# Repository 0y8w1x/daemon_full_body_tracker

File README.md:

# current version (tracker):

# current version (charger/updater):

# firmware
for understanding devicetree and bindings: https://github.com/lmapii/practical-zephyr/tree/main

# notes
to listen to UART: 
minicom -D /dev/ttyUSB0

update firmware over UART with: 
mcumgr-client -d /dev/ttyUSB0 -b 460800 upload build/zephyr/app_update.bin

list with:
mcumgr --conntype serial --connstring "/dev/ttyUSB0,baud=460800" image list

confirm with:
mcumgr --conntype serial --connstring "/dev/ttyUSB0,baud=460800" image confirm c14c40bec9b925ec950af9ccbd3282b68765baeb21c8a0d2d524de6d4da6c468

mcumgr-client -d /dev/ttyUSB0 -b 460800 reset

# NOTE: disabled error handling for "match transceive(&mut *port, &chunk)" in

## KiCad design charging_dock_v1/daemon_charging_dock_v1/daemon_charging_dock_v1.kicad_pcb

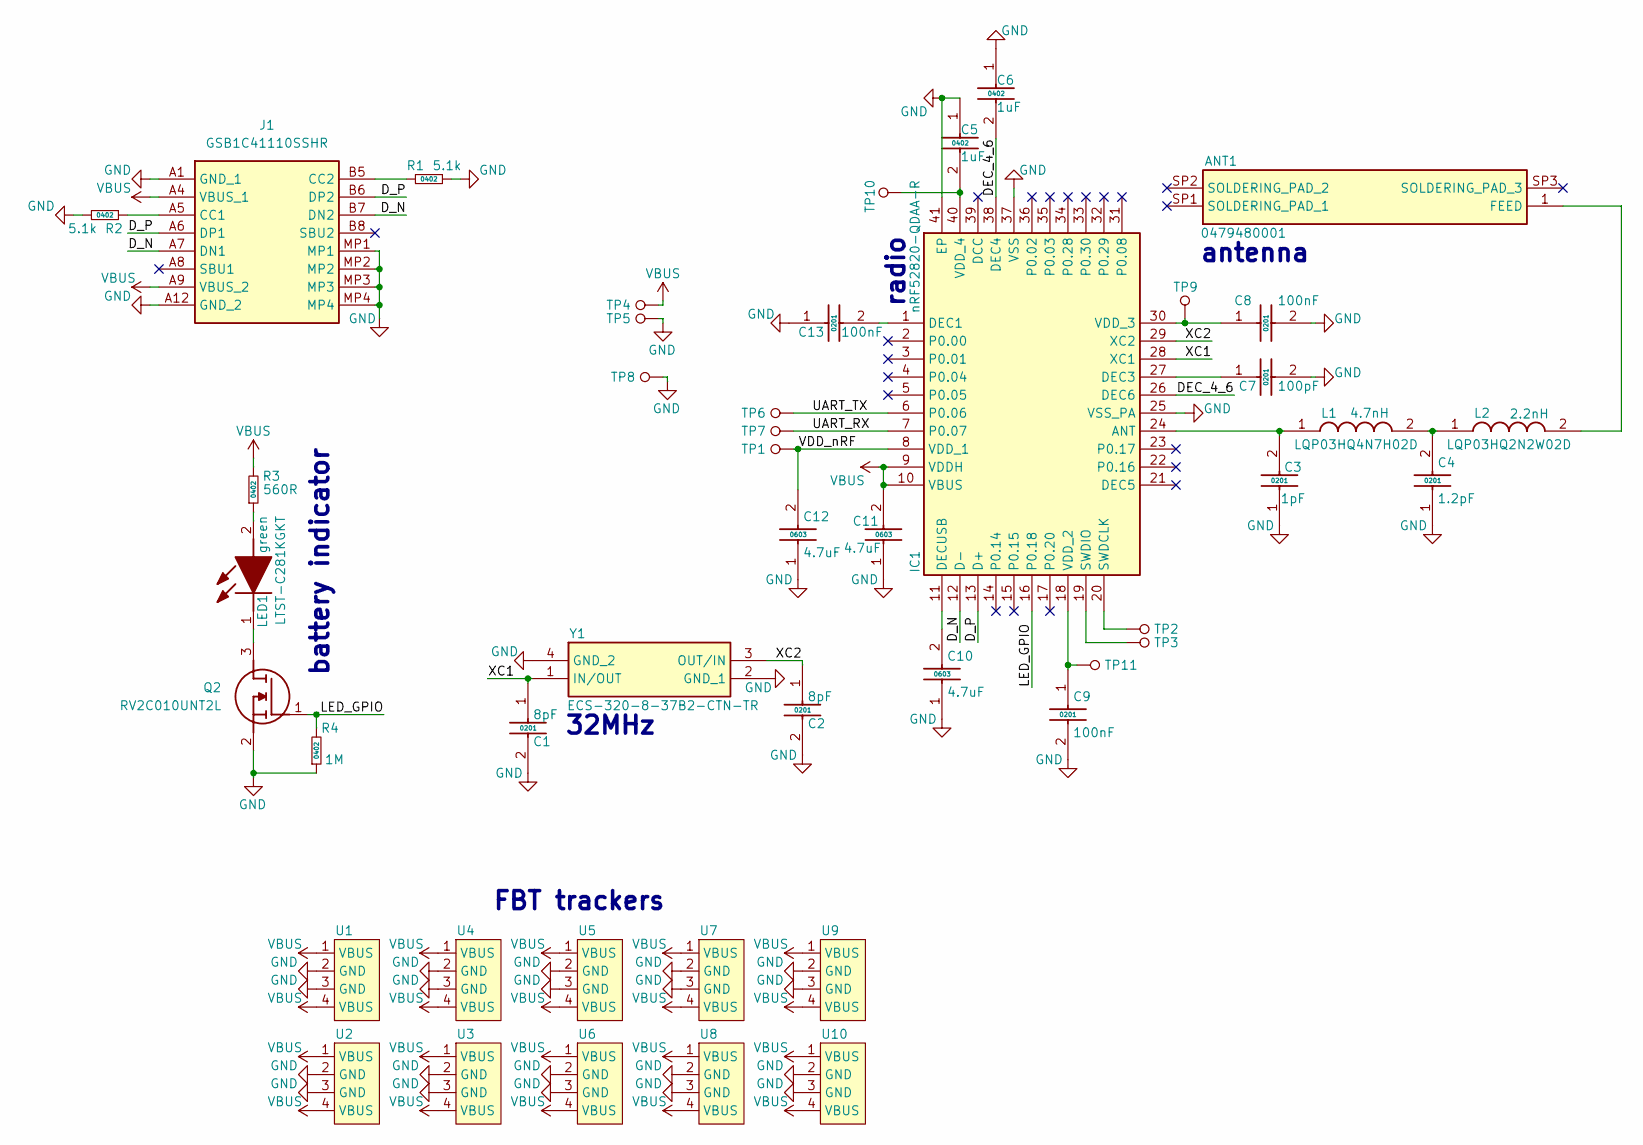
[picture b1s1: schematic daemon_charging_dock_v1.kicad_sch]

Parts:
ANT1: 0479480001; Manufacturer_Part_Number 0479480001; Mouser Part Number N/A
C1, C2: 8pF; CAPC0603X33N
C3: 1pF; CAPC0603X33N; Manufacturer_Part_Number GRM0335C1H1R0WA01D; Mouser Part Number 81-GRM0335C1H1R0WA1D
C4: 1.2pF; CAPC0603X33N; Manufacturer_Part_Number GRM0335C1H1R2WA01D; Mouser Part Number 81-GRM0335C1H1R2WA1D
C5, C6: 1uF; CAPC1005X55N; Manufacturer_Part_Number GRM155C71C105KE11J; Mouser Part Number 81-GRM155C71C105KE11
C7: 100pF; CAPC0603X33N; Manufacturer_Part_Number GRM0335C1E101FA01J; Mouser Part Number 81-GRM0335C1E101FA1J
C8, C9, C13: 100nF; CAPC0603X33N; Manufacturer_Part_Number GRM033R61E104KE14J; Mouser Part Number 81-GRM033R61E104KE4J
C10, C11, C12: 4.7uF; CAPC1608X90N; Manufacturer_Part_Number GRM188Z71C475KE21D; Mouser Part Number 81-GRM188Z71C475KE1D
IC1: nRF52820-QDAA-R; QFN40P500X500X90-41N-D; Manufacturer_Part_Number nRF52820-QDAA-R; Mouser Part Number 949-NRF52820-QDAA-R
J1: GSB1C41110SSHR; Manufacturer_Part_Number GSB1C41110SSHR
L1: 4.7nH; LQP03HQ0N5B02D; Manufacturer_Part_Number LQP03HQ4N7H02D; Mouser Part Number 81-LQP03HQ4N7H02D
L2: 2.2nH; LQP03HQ0N5B02D; Manufacturer_Part_Number LQP03HQ2N2W02D; Mouser Part Number 81-LQP03HQ2N2W02D
LED1: green; LEDC1005X35N; Manufacturer_Part_Number LTST-C281KGKT; Mouser Part Number 859-LTST-C281KGKT
Q2: RV2C010UNT2L; Manufacturer_Part_Number RV2C010UNT2L; Mouser Part Number 755-RV2C010UNT2L
R1, R2: 5.1k; 0402_res
R3: 560R; 0402_res
R4: 1M; 0402_res
TP1, TP2, TP3, TP4, TP5, TP6, TP7, TP8, TP9, TP10, TP11: tp_1mm
U1, U2, U3, U4, U5, U6, U7, U8, U9, U10: fbt_tracker
Y1: ECS-320-8-37B2-CTN-TR; ECS320837B2CTNTR; Manufacturer_Part_Number ECS-320-8-37B2-CTN-TR; Mouser Part Number 520-320-8-37B2-CTNTR

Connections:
/DEC_4_6: C6.2, IC1.26 (DEC6), IC1.38 (DEC4)
/D_N: IC1.12 (D-), J1.A7 (DN1), J1.B7 (DN2)
/D_P: IC1.13 (D+), J1.A6 (DP1), J1.B6 (DP2)
/LED_GPIO: IC1.16 (P0.18), Q2.1 (G), R4.2
/UART_RX: IC1.7 (P0.07), TP7.1
/UART_TX: IC1.6 (P0.06), TP6.1
/VDD_nRF: C12.2, IC1.8 (VDD_1), TP1.1
/XC1: C1.1, IC1.28 (XC1), Y1.1 (IN/OUT)
/XC2: C2.1, IC1.29 (XC2), Y1.3 (OUT/IN)
GND: C1.2, C2.2, C3.1, C4.1, C5.1, C6.1, C7.2, C8.2, C9.2, C10.1, C11.1, C12.1, C13.1, IC1.25 (VSS_PA), IC1.37 (VSS), IC1.41 (EP), J1.A1 (GND_1), J1.A12 (GND_2), J1.MP1, J1.MP2, J1.MP3, J1.MP4, Q2.2 (S), R1.2, R2.2, R4.1, TP5.1, TP8.1, U1.2 (GND), U1.3 (GND), U2.2 (GND), U2.3 (GND), U3.2 (GND), U3.3 (GND), U4.2 (GND), U4.3 (GND), U5.2 (GND), U5.3 (GND), U6.2 (GND), U6.3 (GND), U7.2 (GND), U7.3 (GND), U8.2 (GND), U8.3 (GND), U9.2 (GND), U9.3 (GND), U10.2 (GND), U10.3 (GND), Y1.2 (GND_1), Y1.4 (GND_2)
unnamed: ANT1.1 (FEED), L2.2
unnamed: C4.2, L1.2, L2.1
unnamed: C3.2, IC1.24 (ANT), L1.1
unnamed: C13.2, IC1.1 (DEC1)
unnamed: C7.1, IC1.27 (DEC3)
unnamed: C10.2, IC1.11 (DECUSB)
unnamed: IC1.20 (SWDCLK), TP2.1
unnamed: IC1.19 (SWDIO), TP3.1
unnamed: C9.1, IC1.18 (VDD_2), TP11.1
unnamed: C8.1, IC1.30 (VDD_3), TP9.1
unnamed: C5.2, IC1.40 (VDD_4), TP10.1
unnamed: J1.A5 (CC1), R2.1
unnamed: J1.B5 (CC2), R1.1
unnamed: LED1.2 (A), R3.1
unnamed: LED1.1 (K), Q2.3 (D)
VBUS: C11.2, IC1.9 (VDDH), IC1.10 (VBUS), J1.A4 (VBUS_1), J1.A9 (VBUS_2), R3.2, TP4.1, U1.1 (VBUS), U1.4 (VBUS), U2.1 (VBUS), U2.4 (VBUS), U3.1 (VBUS), U3.4 (VBUS), U4.1 (VBUS), U4.4 (VBUS), U5.1 (VBUS), U5.4 (VBUS), U6.1 (VBUS), U6.4 (VBUS), U7.1 (VBUS), U7.4 (VBUS), U8.1 (VBUS), U8.4 (VBUS), U9.1 (VBUS), U9.4 (VBUS), U10.1 (VBUS), U10.4 (VBUS)

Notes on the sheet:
32MHz
battery indicator
radio
antenna
FBT trackers

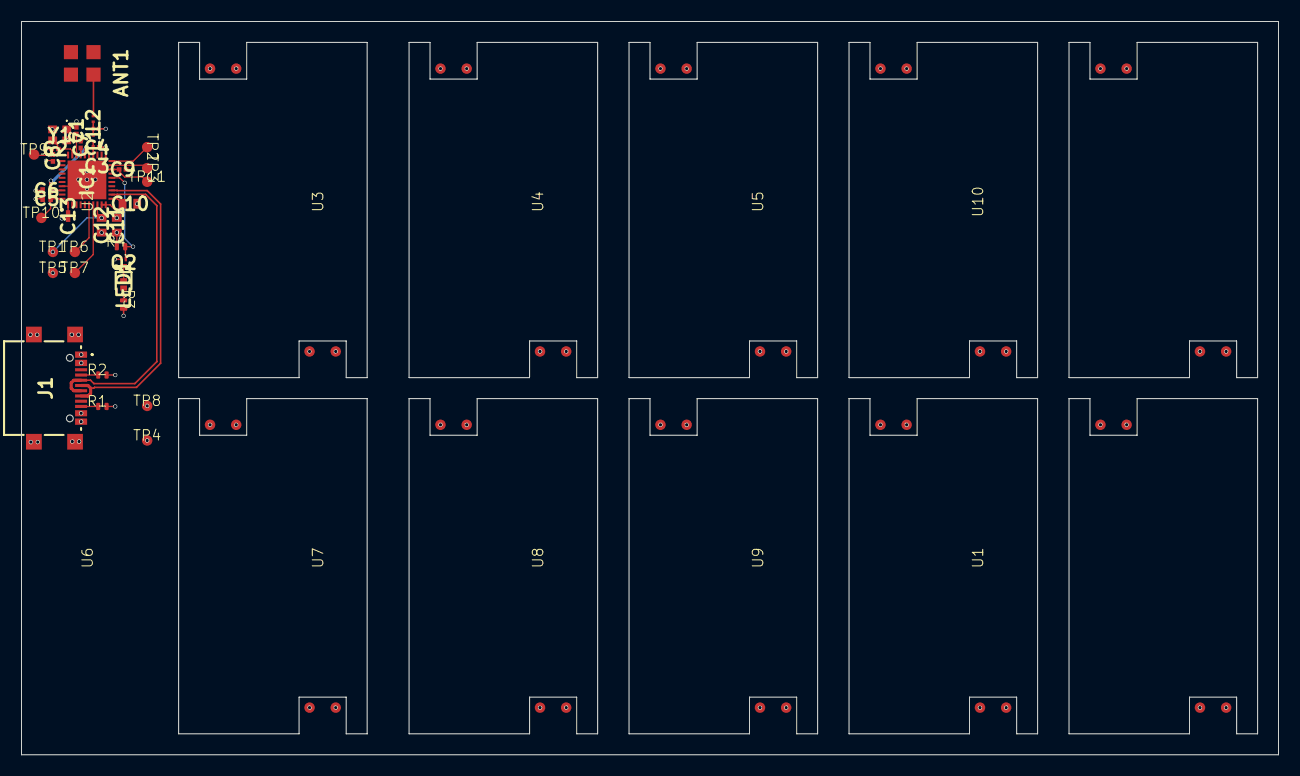
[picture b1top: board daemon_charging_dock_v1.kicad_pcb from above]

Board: 4 copper layers, 120.0 x 70.0 mm, 46 parts (0 on the bottom side), 26 nets.

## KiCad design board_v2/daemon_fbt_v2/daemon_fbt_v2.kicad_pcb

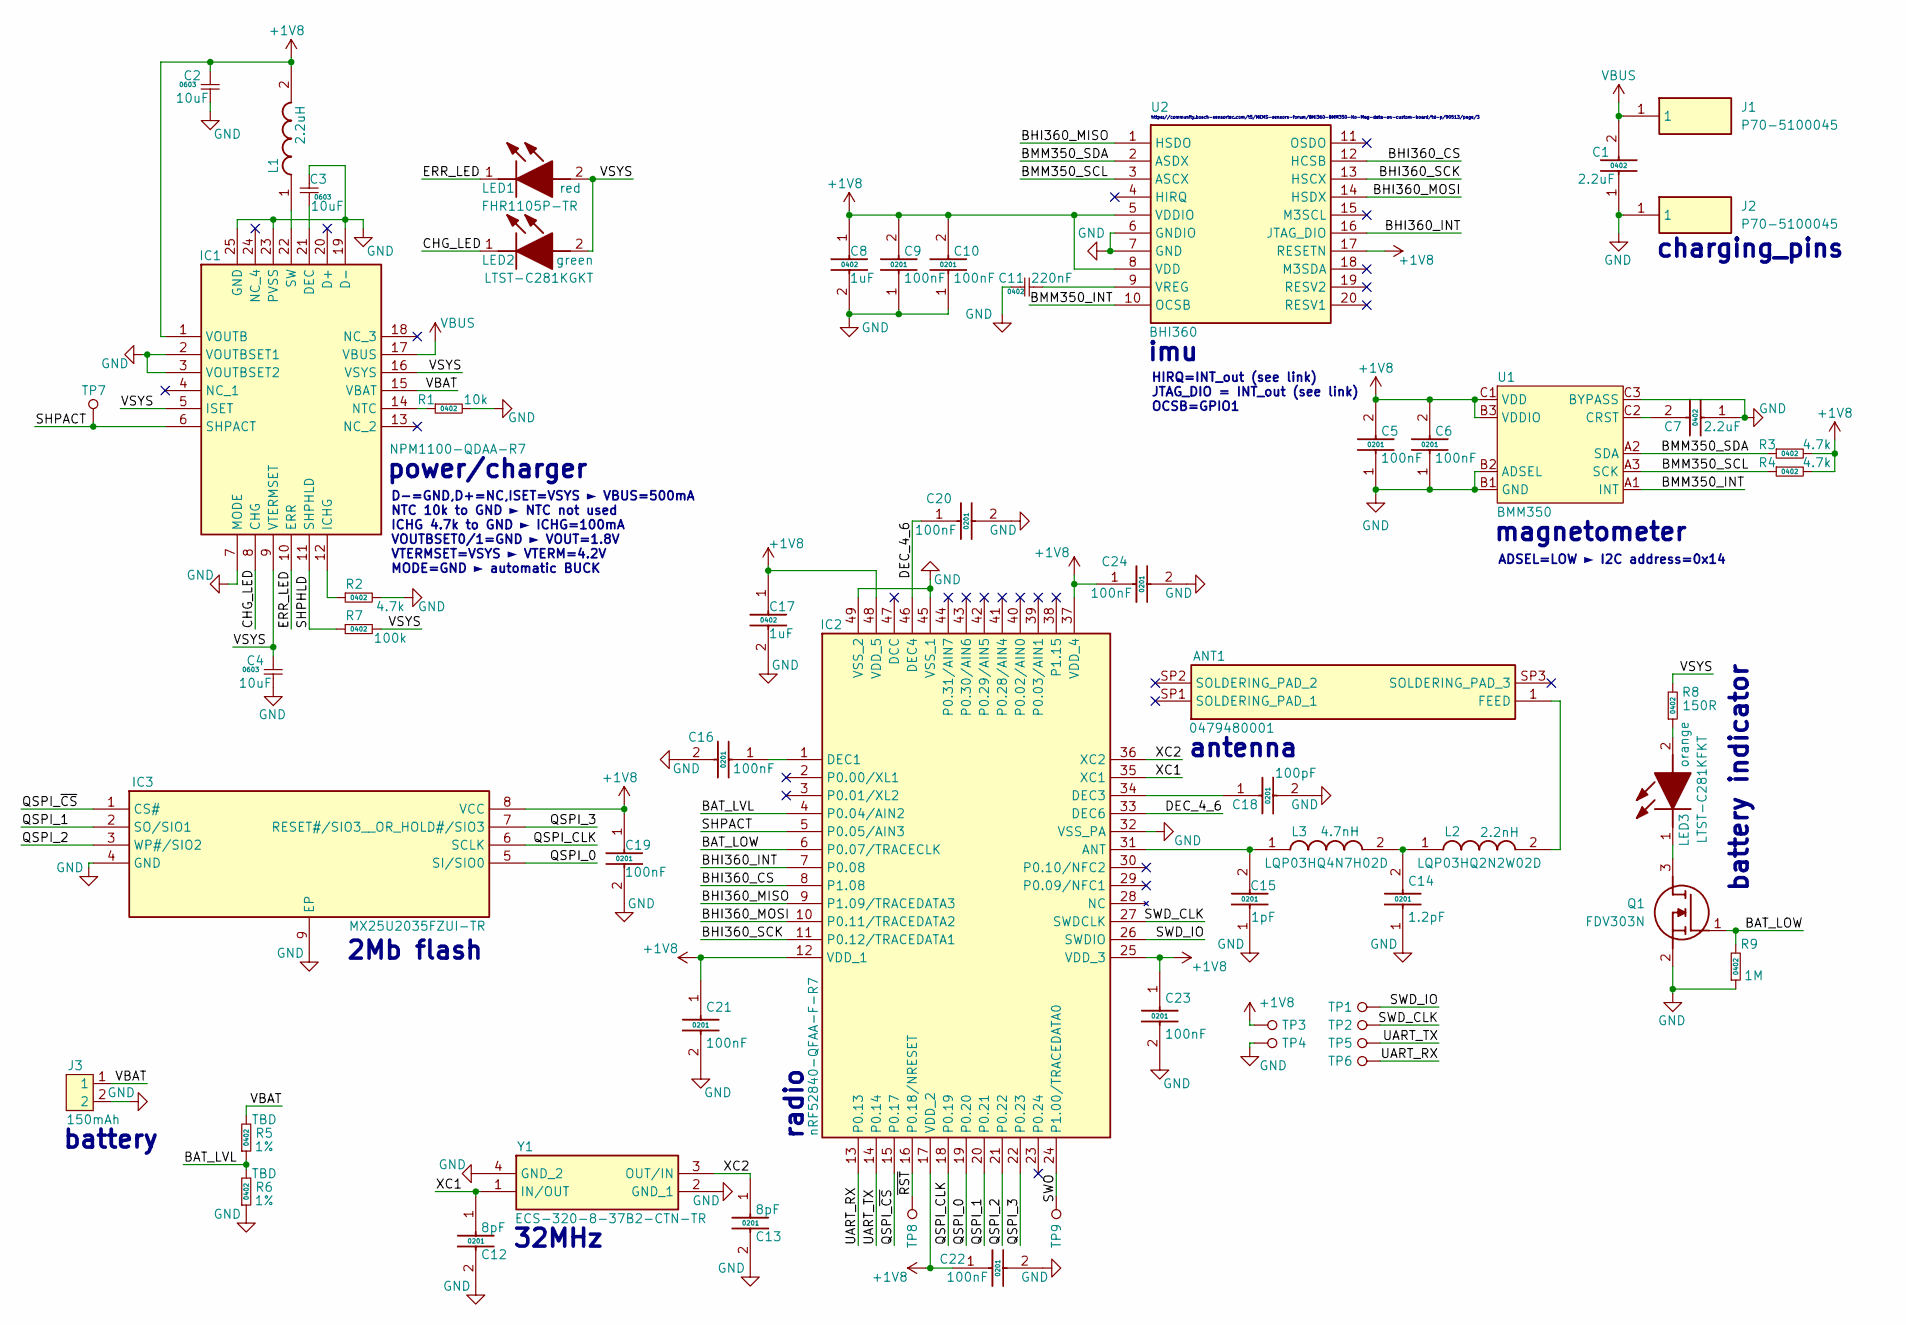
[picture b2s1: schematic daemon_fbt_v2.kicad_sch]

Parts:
ANT1: 0479480001; Manufacturer_Part_Number 0479480001; Mouser Part Number N/A
C1, C7: 2.2uF; CAPC1005X55N; Manufacturer_Part_Number GRM155R61A225KE01J; Mouser Part Number 81-GRM155R61A225K01J
C2, C3, C4: 10uF; 0603_cap
C5, C6, C9, C10, C16, C19, C20, C21, C22, C23, C24: 100nF; CAPC0603X33N; Manufacturer_Part_Number GRM033R61E104KE14J; Mouser Part Number 81-GRM033R61E104KE4J
C8, C17: 1uF; CAPC1005X55N; Manufacturer_Part_Number GRM155C71C105KE11J; Mouser Part Number 81-GRM155C71C105KE11
C11: 220nF; 0402_cap
C12, C13: 8pF; CAPC0603X33N
C14: 1.2pF; CAPC0603X33N; Manufacturer_Part_Number GRM0335C1H1R2WA01D; Mouser Part Number 81-GRM0335C1H1R2WA1D
C15: 1pF; CAPC0603X33N; Manufacturer_Part_Number GRM0335C1H1R0WA01D; Mouser Part Number 81-GRM0335C1H1R0WA1D
C18: 100pF; CAPC0603X33N; Manufacturer_Part_Number GRM0335C1E101FA01J; Mouser Part Number 81-GRM0335C1E101FA1J
IC1: NPM1100-QDAA-R7; QFN50P400X400X90-25N-D; Manufacturer_Part_Number NPM1100-QDAA-R7; Mouser Part Number 949-NPM1100-QDAA-R7
IC2: nRF52840-QFAA-F-R7; QFN40P600X600X95-49N-D; Manufacturer_Part_Number nRF52840-QFAA-F-R7; Mouser Part Number 949-NRF52840QFAAF-R7
IC3: MX25U2035FZUI-TR; SON50P200X300X60-9N; Manufacturer_Part_Number MX25U2035FZUI-TR; Mouser Part Number MX25U2035FZUI-TR
J1, J2: P70-5100045; P705100045; Manufacturer_Part_Number P70-5100045; Mouser Part Number 855-P70-5100045
J3: 150mAh; battery_150mAh
L1: 2.2uH; INDC2012X105N; Manufacturer_Part_Number MLZ2012N2R2LT000; Mouser Part Number 810-MLZ2012N2R2LT000
L2: 2.2nH; LQP03HQ0N5B02D; Manufacturer_Part_Number LQP03HQ2N2W02D; Mouser Part Number 81-LQP03HQ2N2W02D
L3: 4.7nH; LQP03HQ0N5B02D; Manufacturer_Part_Number LQP03HQ4N7H02D; Mouser Part Number 81-LQP03HQ4N7H02D
LED1: red; FHR1105PTR; Manufacturer_Part_Number FHR1105P-TR; Mouser Part Number 327-FHR1105PTR
LED2: green; LEDC1005X35N; Manufacturer_Part_Number LTST-C281KGKT; Mouser Part Number 859-LTST-C281KGKT
LED3: orange; LEDC1005X35N
Q1: FDV303N; SOT96P237X111-3N; Manufacturer_Part_Number FDV303N; Mouser Part Number 512-FDV303N
R1: 10k; 0402_res
R2, R3, R4: 4.7k; 0402_res
R5, R6: TBD; 0402_res; Tolerance 1%
R7: 100k; 0402_res
R8: 150R; 0402_res
R9: 1M; 0402_res
TP1, TP2, TP3, TP4, TP5, TP6, TP7, TP8, TP9: tp_1mm
U1: BMM350
U2: BHI360; Manufacturer_Part_Number BHI360; Mouser Part Number 262-BHI360
Y1: ECS-320-8-37B2-CTN-TR; ECS320837B2CTNTR; Manufacturer_Part_Number ECS-320-8-37B2-CTN-TR; Mouser Part Number 520-320-8-37B2-CTNTR

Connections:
+1V8: C2.2, C5.2, C6.2, C8.1, C9.2, C10.2, C17.1, C19.1, C21.1, C22.1, C23.1, C24.1, IC1.1 (VOUTB), IC2.12 (VDD_1), IC2.17 (VDD_2), IC2.25 (VDD_3), IC2.37 (VDD_4), IC2.48 (VDD_5), IC3.8 (VCC), L1.2, R3.2, R4.2, TP3.1, U1.B3 (VDDIO), U1.C1 (VDD), U2.5 (VDDIO), U2.8 (VDD), U2.17 (RESETN)
/BAT_LOW: IC2.6 (P0.07/TRACECLK), Q1.1 (G), R9.2
/BAT_LVL: IC2.4 (P0.04/AIN2), R5.1, R6.2
/BHI360_CS: IC2.8 (P1.08), U2.12 (HCSB)
/BHI360_INT: IC2.7 (P0.08), U2.16 (JTAG_DIO)
/BHI360_MISO: IC2.9 (P1.09/TRACEDATA3), U2.1 (HSDO)
/BHI360_MOSI: IC2.10 (P0.11/TRACEDATA2), U2.14 (HSDX)
/BHI360_SCK: IC2.11 (P0.12/TRACEDATA1), U2.13 (HSCX)
/BMM350_INT: U1.A1 (INT), U2.10 (OCSB)
/BMM350_SCL: R4.1, U1.A3 (SCK), U2.3 (ASCX)
/BMM350_SDA: R3.1, U1.A2 (SDA), U2.2 (ASDX)
/CHG_LED: IC1.8 (CHG), LED2.1 (K)
/DEC_4_6: C20.1, IC2.33 (DEC6), IC2.46 (DEC4)
/ERR_LED: IC1.10 (ERR), LED1.1 (K)
/QSPI_0: IC2.19 (P0.20), IC3.5 (SI/SIO0)
/QSPI_1: IC2.20 (P0.21), IC3.2 (SO/SIO1)
/QSPI_2: IC2.21 (P0.22), IC3.3 (WP#/SIO2)
/QSPI_3: IC2.22 (P0.23), IC3.7 (RESET#/SIO3__OR_HOLD#/SIO3)
/QSPI_CLK: IC2.18 (P0.19), IC3.6 (SCLK)
/QSPI_~CS: IC2.15 (P0.17), IC3.1 (CS#)
/SHPACT: IC1.6 (SHPACT), IC2.5 (P0.05/AIN3), TP7.1
/SHPHLD: IC1.11 (SHPHLD), R7.1
/SWD_CLK: IC2.27 (SWDCLK), TP2.1
/SWD_IO: IC2.26 (SWDIO), TP1.1
/SWO: IC2.24 (P1.00/TRACEDATA0), TP9.1
/UART_RX: IC2.13 (P0.13), TP6.1
/UART_TX: IC2.14 (P0.14), TP5.1
/VBAT: IC1.15 (VBAT), J3.1, R5.2
/VSYS: C4.2, IC1.5 (ISET), IC1.9 (VTERMSET), IC1.16 (VSYS), LED1.2 (A), LED2.2 (A), R7.2, R8.2
/XC1: C12.1, IC2.35 (XC1), Y1.1 (IN/OUT)
/XC2: C13.1, IC2.36 (XC2), Y1.3 (OUT/IN)
/~RST: IC2.16 (P0.18/NRESET), TP8.1
GND: C1.1, C2.1, C3.2, C4.1, C5.1, C6.1, C7.1, C8.2, C9.1, C10.1, C11.2, C12.2, C13.2, C14.1, C15.1, C16.2, C17.2, C18.2, C19.2, C20.2, C21.2, C22.2, C23.2, C24.2, IC1.2 (VOUTBSET1), IC1.3 (VOUTBSET2), IC1.7 (MODE), IC1.19 (D-), IC1.23 (PVSS), IC1.25 (GND), IC2.32 (VSS_PA), IC2.45 (VSS_1), IC2.49 (VSS_2), IC3.4 (GND), IC3.9 (EP), J2.1, J3.2, Q1.2 (S), R1.2, R2.2, R6.1, R9.1, TP4.1, U1.B1 (GND), U1.B2 (ADSEL), U1.C3 (BYPASS), U2.6 (GNDIO), U2.7 (GND), Y1.2 (GND_1), Y1.4 (GND_2)
unnamed: ANT1.1 (FEED), L2.2
unnamed: C14.2, L2.1, L3.2
unnamed: C3.1, IC1.21 (DEC)
unnamed: IC1.12 (ICHG), R2.1
unnamed: IC1.14 (NTC), R1.1
unnamed: IC1.22 (SW), L1.1
unnamed: C15.2, IC2.31 (ANT), L3.1
unnamed: C16.1, IC2.1 (DEC1)
unnamed: C18.1, IC2.34 (DEC3)
unnamed: LED3.2 (A), R8.1
unnamed: LED3.1 (K), Q1.3 (D)
unnamed: C7.2, U1.C2 (CRST)
unnamed: C11.1, U2.9 (VREG)
VBUS: C1.2, IC1.17 (VBUS), J1.1

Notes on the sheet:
battery
D-=GND,D+=NC,ISET=VSYS ► VBUS=500mA NTC 10k to GND ► NTC not used ICHG 4.7k to GND ► ICHG=100mA VOUTBSET0/1=GND ► VOUT=1.8V VTERMSET=VSYS ► VTERM=4.2V MODE=GND ► automatic BUCK
ADSEL=LOW ► I2C address=0x14
https://community.bosch-sensortec.com/t5/MEMS-sensors-forum/BHI360-BMM350-No-Mag-data-on-custom-board/td-p/90513/page/3
battery indicator
32MHz
antenna
HIRQ=INT_out (see link) JTAG_DIO = INT_out (see link) OCSB=GPIO1
magnetometer
radio
2Mb flash
charging_pins
imu
power/charger

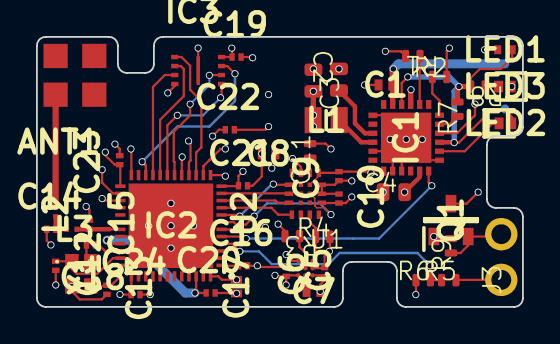
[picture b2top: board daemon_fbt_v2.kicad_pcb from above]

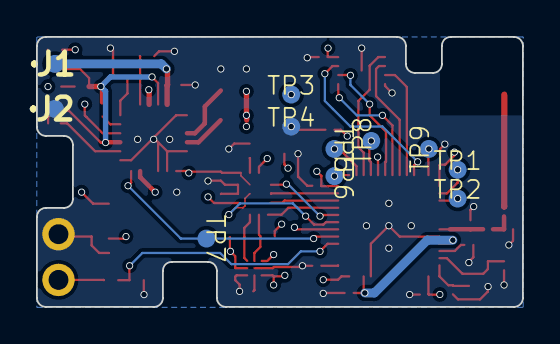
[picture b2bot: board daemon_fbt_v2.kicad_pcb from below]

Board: 4 copper layers, 27.0 x 15.0 mm, 59 parts (11 on the bottom side), 47 nets.

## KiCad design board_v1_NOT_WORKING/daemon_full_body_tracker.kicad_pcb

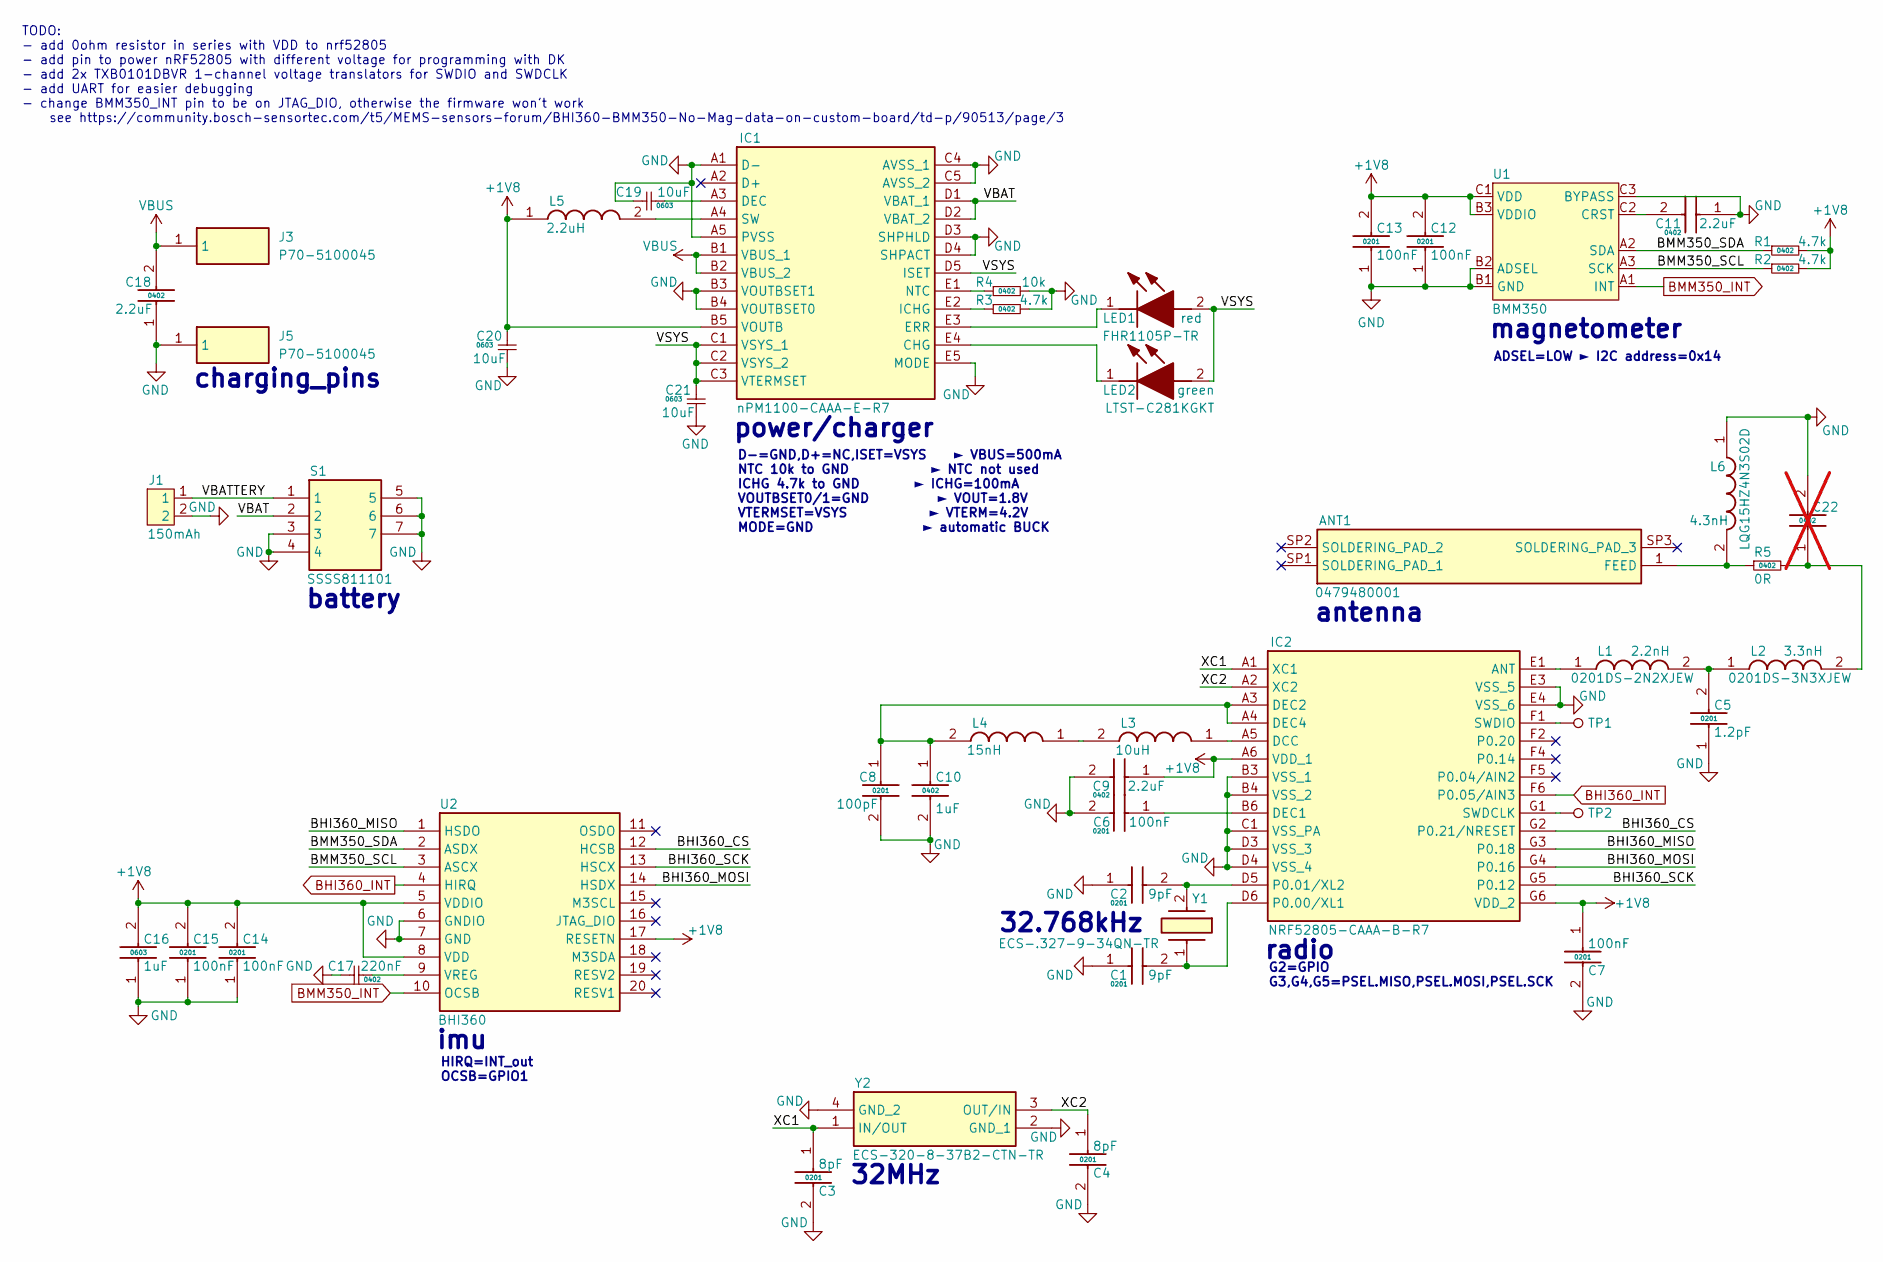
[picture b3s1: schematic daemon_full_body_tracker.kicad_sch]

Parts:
ANT1: 0479480001; Manufacturer_Part_Number 0479480001; Mouser Part Number N/A
C1, C2: 9pF; CAPC0603X33N
C3, C4: 8pF; CAPC0603X33N
C5: 1.2pF; CAPC0603X33N; Manufacturer_Part_Number GRM0335C1E1R2BA01D; Mouser Part Number 81-GRM0335C1E1R2BA1D
C6, C7, C12, C13, C14, C15: 100nF; CAPC0603X33N; Manufacturer_Part_Number GRM033R61E104KE14J; Mouser Part Number 81-GRM033R61E104KE4J
C8: 100pF; CAPC0603X33N; Manufacturer_Part_Number GRM0335C1E101FA01J; Mouser Part Number 81-GRM0335C1E101FA1J
C9, C11, C18: 2.2uF; CAPC1005X55N; Manufacturer_Part_Number GRM155R61E225KE11D; Mouser Part Number 81-GRM155R61E225KE1D
C10: 1uF; CAPC1005X55N; Manufacturer_Part_Number GRM155C71C105KE11J; Mouser Part Number 81-GRM155C71C105KE11
C16: 1uF; CAPC1608X90N; Manufacturer_Part_Number 0603ZD105JAT2A; Mouser Part Number 581-0603ZD105JAT2A
C17: 220nF; 0402_cap
C19, C20, C21: 10uF; 0603_cap
C22: CAPC1005X55N; Manufacturer_Part_Number GRM155C71C105KE11J; Mouser Part Number 81-GRM155C71C105KE11; not fitted
IC1: nPM1100-CAAA-E-R7; BGA25C40P5X5_208X208X52; Manufacturer_Part_Number nPM1100-CAAA-E-R7; Mouser Part Number 949-NPM1100-CAAA-R7
IC2: NRF52805-CAAA-B-R7; NRF52805CAAAR7
J1: 150mAh; battery_150mAh
J3, J5: P70-5100045; P705100045; Manufacturer_Part_Number P70-5100045; Mouser Part Number 855-P70-5100045
L1: 2.2nH; INDC0605X45N; Manufacturer_Part_Number 0201DS-2N2XJEW; Mouser Part Number 994-0201DS-2N2XJEW
L2: 3.3nH; INDC0605X45N; Manufacturer_Part_Number 0201DS-3N3XJEW; Mouser Part Number 994-0201DS-3N3XJEW
L3: 10uH; INDM2520X190N; Manufacturer_Part_Number NLV25T-100J-EF; Mouser Part Number 810-NLV25T-100J-EF
L4: 15nH; LQW15CNR20J00B; Manufacturer_Part_Number LQW15AN15NH00D; Mouser Part Number 81-LQW15AN15NH00D
L5: 2.2uH; INDC2012X105N; Manufacturer_Part_Number MLZ2012N2R2LT000; Mouser Part Number 810-MLZ2012N2R2LT000
L6: 4.3nH; LQG15WH0N7B02D; Manufacturer_Part_Number LQG15HZ4N3S02D
LED1: red; FHR1105PTR; Manufacturer_Part_Number FHR1105P-TR; Mouser Part Number 327-FHR1105PTR
LED2: green; LEDC1005X35N; Manufacturer_Part_Number LTST-C281KGKT; Mouser Part Number 859-LTST-C281KGKT
R1, R2, R3: 4.7k; 0402_res
R4: 10k; 0402_res
R5: 0R; 0402_res
S1: SSSS811101; Manufacturer_Part_Number SSSS811101; Mouser Part Number 688-SSSS811101
TP1, TP2: tp_1mm
U1: BMM350
U2: BHI360; Manufacturer_Part_Number BHI360; Mouser Part Number 262-BHI360
Y1: ECS-.327-9-34QN-TR; ECS327934QNTR; Manufacturer_Part_Number ECS-.327-9-34QN-TR; Mouser Part Number 520-.327-9-34QNT
Y2: ECS-320-8-37B2-CTN-TR; ECS320837B2CTNTR; Manufacturer_Part_Number ECS-320-8-37B2-CTN-TR; Mouser Part Number 520-320-8-37B2-CTNTR

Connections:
+1V8: C7.1, C9.1, C12.2, C13.2, C14.2, C15.2, C16.2, C20.2, IC1.B5 (VOUTB), IC2.A6 (VDD_1), IC2.G6 (VDD_2), L5.1, R1.2, R2.2, U1.B3 (VDDIO), U1.C1 (VDD), U2.5 (VDDIO), U2.8 (VDD), U2.17 (RESETN)
/BHI360_CS: IC2.G2 (P0.21/NRESET), U2.12 (HCSB)
/BHI360_MISO: IC2.G3 (P0.18), U2.1 (HSDO)
/BHI360_MOSI: IC2.G4 (P0.16), U2.14 (HSDX)
/BHI360_SCK: IC2.G5 (P0.12), U2.13 (HSCX)
/BMM350_SCL: R2.1, U1.A3 (SCK), U2.3 (ASCX)
/BMM350_SDA: R1.1, U1.A2 (SDA), U2.2 (ASDX)
/VBAT: IC1.D1 (VBAT_1), IC1.D2 (VBAT_2), S1.2
/VBATTERY: J1.1, S1.1
/VSYS: C21.2, IC1.C1 (VSYS_1), IC1.C2 (VSYS_2), IC1.C3 (VTERMSET), IC1.D5 (ISET), LED1.2 (A), LED2.2 (A)
/XC1: C3.1, IC2.A1 (XC1), Y2.1 (IN/OUT)
/XC2: C4.1, IC2.A2 (XC2), Y2.3 (OUT/IN)
BHI360_INT: IC2.F6 (P0.05/AIN3), U2.4 (HIRQ)
BMM350_INT: U1.A1 (INT), U2.10 (OCSB)
GND: C1.1, C2.1, C3.2, C4.2, C5.1, C6.2, C7.2, C8.2, C9.2, C10.2, C11.1, C12.1, C13.1, C14.1, C15.1, C16.1, C17.2, C18.1, C19.1, C20.1, C21.1, C22.2, IC1.A1 (D-), IC1.A5 (PVSS), IC1.B3 (VOUTBSET1), IC1.B4 (VOUTBSET0), IC1.C4 (AVSS_1), IC1.C5 (AVSS_2), IC1.D3 (SHPHLD), IC1.D4 (SHPACT), IC1.E5 (MODE), IC2.B3 (VSS_1), IC2.B4 (VSS_2), IC2.C1 (VSS_PA), IC2.D3 (VSS_3), IC2.D4 (VSS_4), IC2.E3 (VSS_5), IC2.E4 (VSS_6), J1.2, J5.1, L6.1, R3.2, R4.2, S1.3, S1.4, S1.5, S1.6, S1.7, U1.B1 (GND), U1.B2 (ADSEL), U1.C3 (BYPASS), U2.6 (GNDIO), U2.7 (GND), Y2.2 (GND_1), Y2.4 (GND_2)
unnamed: ANT1.1 (FEED), L6.2, R5.1
unnamed: C5.2, L1.2, L2.1
unnamed: C22.1, L2.2, R5.2
unnamed: IC1.E4 (CHG), LED2.1 (K)
unnamed: C19.2, IC1.A3 (DEC)
unnamed: IC1.E3 (ERR), LED1.1 (K)
unnamed: IC1.E2 (ICHG), R3.1
unnamed: IC1.E1 (NTC), R4.1
unnamed: IC1.A4 (SW), L5.2
unnamed: IC2.E1 (ANT), L1.1
unnamed: IC2.A5 (DCC), L3.1
unnamed: C6.1, IC2.B6 (DEC1)
unnamed: C8.1, C10.1, IC2.A3 (DEC2), IC2.A4 (DEC4), L4.2
unnamed: C1.2, IC2.D6 (P0.00/XL1), Y1.1 (OUT/IN)
unnamed: C2.2, IC2.D5 (P0.01/XL2), Y1.2 (OUT/IN)
unnamed: IC2.G1 (SWDCLK), TP2.1
unnamed: IC2.F1 (SWDIO), TP1.1
unnamed: L3.2, L4.1
unnamed: C11.2, U1.C2 (CRST)
unnamed: C17.1, U2.9 (VREG)
VBUS: C18.2, IC1.B1 (VBUS_1), IC1.B2 (VBUS_2), J3.1

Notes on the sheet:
D-=GND,D+=NC,ISET=VSYS ► VBUS=500mA NTC 10k to GND ► NTC not used ICHG 4.7k to GND ► ICHG=100mA VOUTBSET0/1=GND ► VOUT=1.8V VTERMSET=VSYS ► VTERM=4.2V MODE=GND ► automatic BUCK
32.768kHz
TODO: - add 0ohm resistor in series with VDD to nrf52805 - add pin to power nRF52805 with different voltage for programming with DK - add 2x TXB0101DBVR 1-channel voltage translators for SWDIO and SWDCLK - add UART for easier debugging - change BMM350_INT pin to be on JTAG_DIO, otherwise the firmwa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
HIRQ=INT_out OCSB=GPIO1
G2=GPIO G3,G4,G5=PSEL.MISO,PSEL.MOSI,PSEL.SCK
radio
power/charger
ADSEL=LOW ► I2C address=0x14
magnetometer
battery
antenna
charging_pins
imu
32MHz

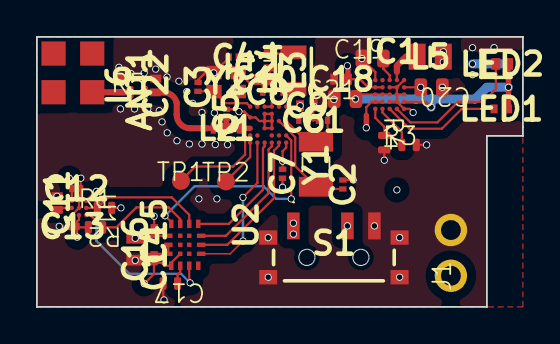
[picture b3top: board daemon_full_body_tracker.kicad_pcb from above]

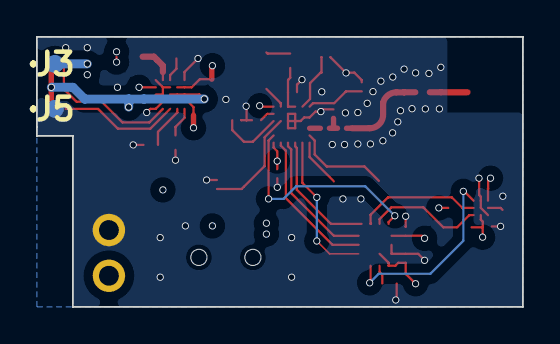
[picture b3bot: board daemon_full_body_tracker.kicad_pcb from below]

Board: 4 copper layers, 27.0 x 15.0 mm, 48 parts (2 on the bottom side), 36 nets.

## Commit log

2024-04-20 init
2024-04-21 added todo list for next revision
2024-04-22 updated todo list
2024-04-23 add project skeleton for nRF52805 firmware
2024-04-25 add board specific files
2024-04-25 add another todo item to the list
2024-04-25 successfully run modified ESB example on custom nrf52805 board
2024-04-26 deprecated board_v1
2024-04-26 reference old images correctly
2024-04-27 redesigned schematics; nrf52805->nrf52840; chose simpler footprints for both nrf ICs; added battery sensing/indicator; fixed bugs
2024-04-27 updated schematic pdf
2024-04-27 update flash memory from 64Mbit to 2Mbit and create footprint
2024-04-27 added more mfr. no. into the data fields
2024-04-27 fixed picture paths
2024-04-27 reduce price of some components
2024-04-27 finished redesign; lets hope jlcpcb doesn't kill me
2024-04-27 change image location
2024-04-28 redesign again, because there is no reason to make it very small; bc the size is battery limited
2024-04-28 fix unaligned pogo pins
2024-04-29 added charging dock board
2024-07-27 changed files
2024-07-27 changed filed
